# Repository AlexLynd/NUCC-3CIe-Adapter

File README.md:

# 3CIe: A PCIe Mini to PCIe 1x Adapter
But 3 of them specifically designed to slot [Intel 7260]() WiFi cards to an AMD motherboard.

## Ordering Instructions
All production files can be found under `/export`.
|File Name|File Type|Desc|
|---|---|---|
|`Vx-3CIE_GBR-Rx`|PCB Production files (Gerber)||
|`Vx-3CIE_CPL-Rx`|Component Placement List (CPL)|JLCPCB export standard|
|`Vx-3CIE_BOM-Rx`|Bill of Materials (BOM)|Using JLCPCB Parts|

## To-Do
- [x] Fix zone fill
- [ ] Fix spelling
- [x] Add exports / models
- [ ] Fix paths

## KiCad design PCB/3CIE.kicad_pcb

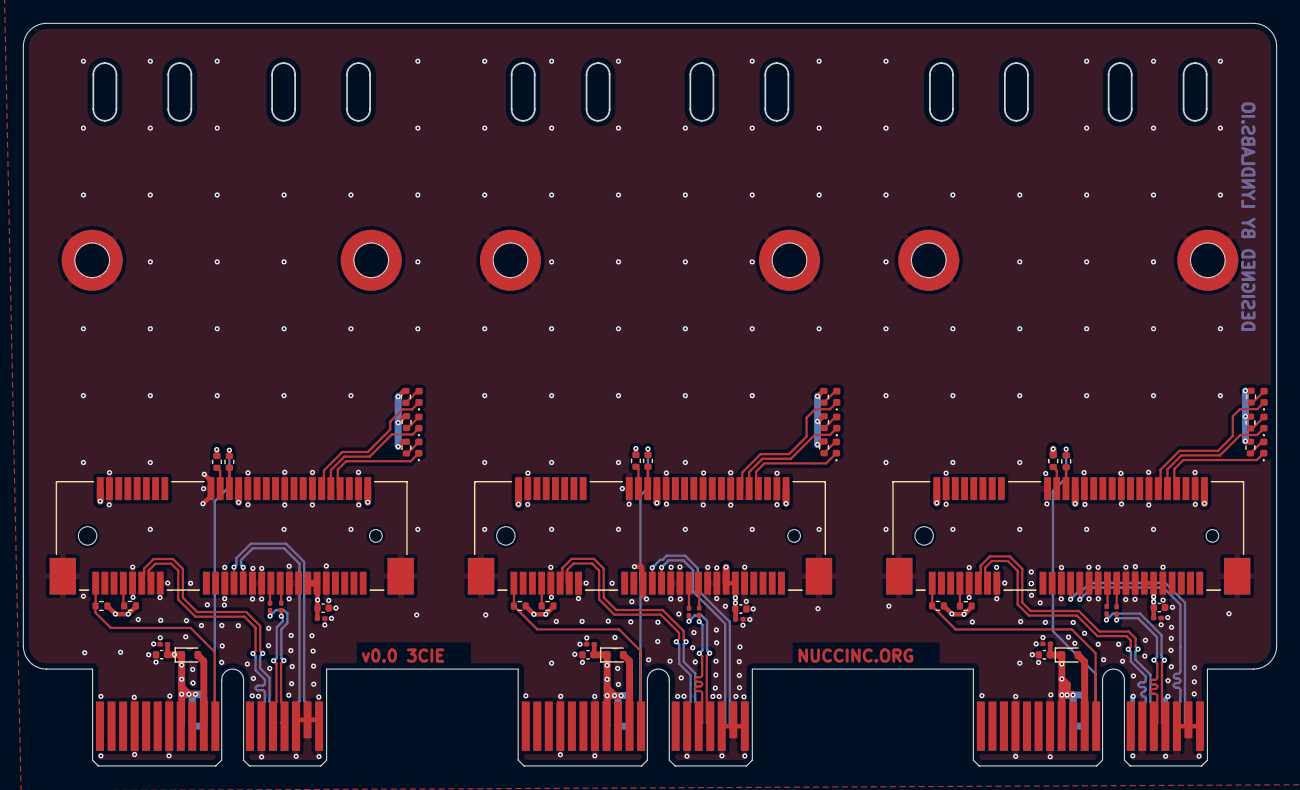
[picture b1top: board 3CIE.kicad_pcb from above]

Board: 4 copper layers, 108.7 x 64.4 mm, 57 parts (0 on the bottom side), 62 nets.

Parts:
C1, C2, C4, C6, C7, C9, C11, C13, C15, C16, C17, C18: 100nF; C_0201_0603Metric
C3, C12, C14: 10uF; C_0402_1005Metric
C5, C8, C10: 47uF; C_0402_1005Metric
D1, D2, D3: D_Schottky; D_SOD-523
D7, D8, D9, D10, D11, D12, D13, D14, D15: LED; LED_0402_1005Metric
J1, J2, J3: Bus_PCI_Express_x1; BUS_PCIexpress_x1
J4, J5, J6: Bus_PCI_Express_Mini; BUS_PCI_Express_Mini_Half
R1, R2, R7, R8, R13, R14, R19, R20, R21: 10K; R_0402_1005Metric
R3, R9, R15: 100; R_0402_1005Metric
R4, R5, R6, R10, R11, R12, R16, R17, R18: 330; R_0402_1005Metric

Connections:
+3V3: C3.1, C4.2, C5.1, C6.2, C7.2, C8.1, C9.2, C10.1, C11.2, C12.1, C13.2, C14.1, D1.1 (K), D2.1 (K), D3.1 (K), J1.A9 (+3.3V), J1.A10 (+3.3V), J1.B8 (+3.3V), J2.A9 (+3.3V), J2.A10 (+3.3V), J2.B8 (+3.3V), J3.A9 (+3.3V), J3.A10 (+3.3V), J3.B8 (+3.3V), J4.2 (+3V3AUX), J4.24 (+3V3AUX), J4.39 (+3V3AUX), J4.41 (+3V3AUX), J4.52 (+3V3AUX), J5.2 (+3V3AUX), J5.24 (+3V3AUX), J5.39 (+3V3AUX), J5.41 (+3V3AUX), J5.52 (+3V3AUX), J6.2 (+3V3AUX), J6.24 (+3V3AUX), J6.39 (+3V3AUX), J6.41 (+3V3AUX), J6.52 (+3V3AUX), R1.1, R2.2, R4.2, R5.2, R6.2, R7.1, R8.2, R10.2, R11.2, R12.2, R13.1, R14.2, R16.2, R17.2, R18.2, R19.1, R20.1, R21.1
GND: C3.2, C4.1, C5.2, C6.1, C7.1, C8.2, C9.1, C10.2, C11.1, C12.2, C13.1, C14.2, J1.A1 (~PRSNT1), J1.A4 (GND), J1.A12 (GND), J1.A15 (GND), J1.A18 (GND), J1.B4 (GND), J1.B7 (GND), J1.B13 (GND), J1.B16 (GND), J1.B17 (~PRSNT2), J1.B18 (GND), J2.A1 (~PRSNT1), J2.A4 (GND), J2.A12 (GND), J2.A15 (GND), J2.A18 (GND), J2.B4 (GND), J2.B7 (GND), J2.B13 (GND), J2.B16 (GND), J2.B17 (~PRSNT2), J2.B18 (GND), J3.A1 (~PRSNT1), J3.A4 (GND), J3.A12 (GND), J3.A15 (GND), J3.A18 (GND), J3.B4 (GND), J3.B7 (GND), J3.B13 (GND), J3.B16 (GND), J3.B17 (~PRSNT2), J3.B18 (GND), J4.4 (GND), J4.9 (GND), J4.15 (GND), J4.18 (GND), J4.21 (GND), J4.26 (GND), J4.27 (GND), J4.29 (GND), J4.34 (GND), J4.35 (GND), J4.37 (GND), J4.40 (GND), J4.43 (GND), J4.50 (GND), J4.MP, J5.4 (GND), J5.9 (GND), J5.15 (GND), J5.18 (GND), J5.21 (GND), J5.26 (GND), J5.27 (GND), J5.29 (GND), J5.34 (GND), J5.35 (GND), J5.37 (GND), J5.40 (GND), J5.43 (GND), J5.50 (GND), J5.MP, J6.4 (GND), J6.9 (GND), J6.15 (GND), J6.18 (GND), J6.21 (GND), J6.26 (GND), J6.27 (GND), J6.29 (GND), J6.34 (GND), J6.35 (GND), J6.37 (GND), J6.40 (GND), J6.43 (GND), J6.50 (GND), J6.MP
unnamed: D1.2 (A), J1.B10 (3.3Vaux)
unnamed: D2.2 (A), J2.B10 (3.3Vaux)
unnamed: D3.2 (A), J3.B10 (3.3Vaux)
unnamed: D7.2 (A), R4.1
unnamed: D7.1 (K), J4.46 (~LED_WPAN)
unnamed: D8.2 (A), R5.1
unnamed: D8.1 (K), J4.44 (~LED_WLAN)
unnamed: D9.2 (A), R6.1
unnamed: D9.1 (K), J4.42 (~LED_WWAN)
unnamed: D10.2 (A), R10.1
unnamed: D10.1 (K), J5.46 (~LED_WPAN)
unnamed: D11.2 (A), R11.1
unnamed: D11.1 (K), J5.44 (~LED_WLAN)
unnamed: D12.2 (A), R12.1
unnamed: D12.1 (K), J5.42 (~LED_WWAN)
unnamed: D13.2 (A), R16.1
unnamed: D13.1 (K), J6.46 (~LED_WPAN)
unnamed: D14.2 (A), R17.1
unnamed: D14.1 (K), J6.44 (~LED_WLAN)
unnamed: D15.2 (A), R18.1
unnamed: D15.1 (K), J6.42 (~LED_WWAN)
unnamed: C2.2, J4.31 (PETn0)
unnamed: C1.2, J4.33 (PETp0)
unnamed: J4.7 (~CLKREQ), R19.2
unnamed: J4.22 (~PERST), R3.2
unnamed: J4.20 (~W_DISABLE), R2.1
unnamed: C15.2, J5.31 (PETn0)
unnamed: C16.2, J5.33 (PETp0)
unnamed: J5.7 (~CLKREQ), R20.2
unnamed: J5.22 (~PERST), R9.2
unnamed: J5.20 (~W_DISABLE), R8.1
unnamed: C17.2, J6.31 (PETn0)
unnamed: C18.2, J6.33 (PETp0)
unnamed: J6.7 (~CLKREQ), R21.2
unnamed: J6.22 (~PERST), R15.2
unnamed: J6.20 (~W_DISABLE), R14.1
PER0-1+: J1.A16 (PERp0), J4.25 (PERp0)
PER0-1-: J1.A17 (PERn0), J4.23 (PERn0)
PER0-2+: J2.A16 (PERp0), J5.25 (PERp0)
PER0-2-: J2.A17 (PERn0), J5.23 (PERn0)
PER0-3+: J3.A16 (PERp0), J6.25 (PERp0)
PER0-3-: J3.A17 (PERn0), J6.23 (PERn0)
PERST1: J1.A11 (~PERST), R3.1
PERST2: J2.A11 (~PERST), R9.1
PERST3: J3.A11 (~PERST), R15.1
PET0-1+: C1.1, J1.B14 (PETp0)
PET0-1-: C2.1, J1.B15 (PETn0)
PET0-2+: C16.1, J2.B14 (PETp0)
PET0-2-: C15.1, J2.B15 (PETn0)
PET0-3+: C18.1, J3.B14 (PETp0)
PET0-3-: C17.1, J3.B15 (PETn0)
RFCLK1+: J1.A13 (REFCLK+), J4.13 (REFCLK+)
RFCLK1-: J1.A14 (REFCLK-), J4.11 (REFCLK-)
RFCLK2+: J2.A13 (REFCLK+), J5.13 (REFCLK+)
RFCLK2-: J2.A14 (REFCLK-), J5.11 (REFCLK-)
RFCLK3+: J3.A13 (REFCLK+), J6.13 (REFCLK+)
RFCLK3-: J3.A14 (REFCLK-), J6.11 (REFCLK-)
WAKE1: J1.B11 (~WAKE), R1.2
WAKE2: J2.B11 (~WAKE), J5.1 (~WAKE), R7.2
WAKE3: J3.B11 (~WAKE), J6.1 (~WAKE), R13.2

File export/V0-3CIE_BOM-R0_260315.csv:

Designator,Value,Footprint,JLCPCB Part #
"C1,C2,C4,C6,C7,C9,C11,C13,C15,C16,C17,C18",100nF,Capacitor_SMD:C_0201_0603Metric,C22435929
"C3,C12,C14",10uF,Capacitor_SMD:C_0402_1005Metric,C315248
"C5,C8,C10",22uF,Capacitor_SMD:C_0402_1005Metric,C105226
"D1,D2,D3",D_Schottky,Diode_SMD:D_SOD-523,C122862
"D7,D8,D9,D10,D11,D12,D13,D14,D15",LED,LED_SMD:LED_0402_1005Metric,C30584803
"J4,J5,J6",Bus_PCI_Express_Mini,,C920235
"R1,R2,R7,R8,R13,R14,R19,R20,R21",10K,Resistor_SMD:R_0402_1005Metric,C60490
"R3,R9,R15",100,Resistor_SMD:R_0402_1005Metric,C106232
"R4,R5,R6,R10,R11,R12,R16,R17,R18",330,Resistor_SMD:R_0402_1005Metric,C105875

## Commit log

2026-03-15 push initial design files
2026-03-15 Correct spelling of 'PCIe' in README
2026-03-15 update todo
2026-03-15 fix logo placement
2026-03-16 push production files / fix board fill
2026-03-16 Revise README with ordering and production file info
    Updated ordering instructions and added production file details.
